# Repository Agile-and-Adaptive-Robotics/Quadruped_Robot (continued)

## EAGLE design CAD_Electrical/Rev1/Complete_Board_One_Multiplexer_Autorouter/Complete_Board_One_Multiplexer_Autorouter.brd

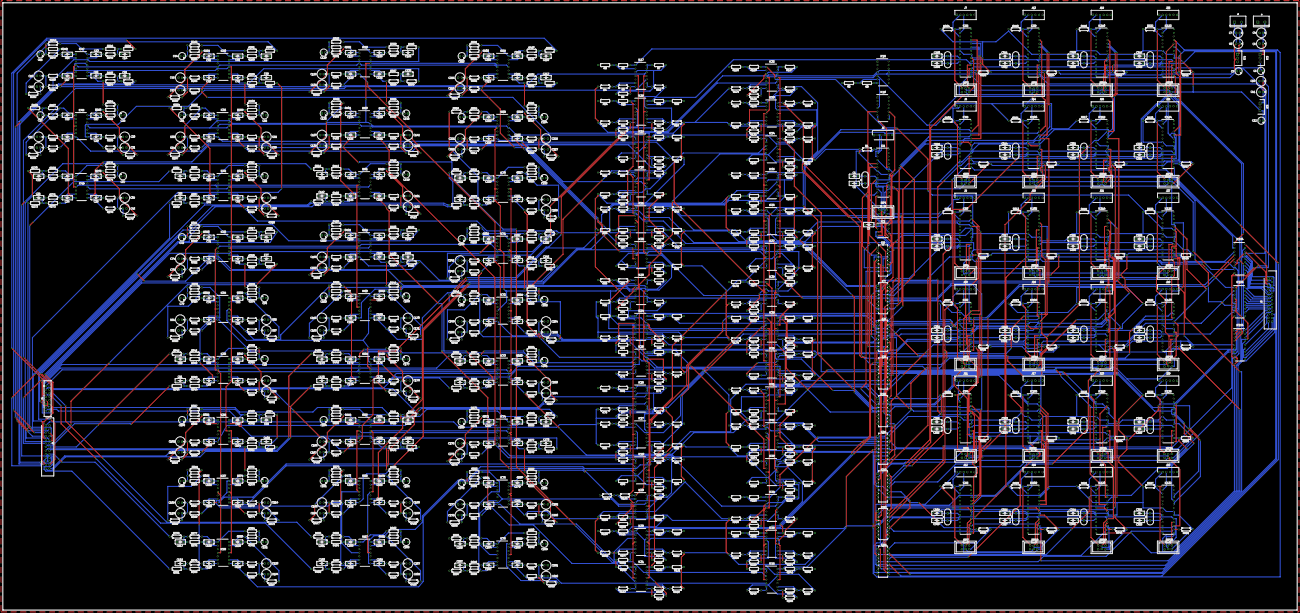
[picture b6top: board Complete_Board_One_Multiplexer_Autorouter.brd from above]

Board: 2 copper layers, 916.9 x 430.2 mm, 1174 parts (0 on the bottom side), 890 nets.

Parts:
C1, C2, C3, C13, C14, C15, C17, C20, C21, C22, C24, C27, C29, C32, C33, C34, C35, C36, C38, C41, C42, C43, C45, C48, C49, C50, C52, C55, C57, C60, C61, C62, C63, C64, C66, C69, C70, C71, C73, C76, C77, C78, C80, C83, C85, C88, C89, C90, C91, C92, C94, C97, C98, C99, C101, C104, C105, C106, C108, C111, C113, C116, C117, C118, C119, C120, C122, C125, C126, C127, C129, C132, C133, C134, C136, C139, C141, C144, C145, C146, C147, C148, C150, C153, C154, C155, C157, C160, C161, C162, C164, C167, C169, C172, C173, C174, C175, C176, C178, C181, C182, C183, C185, C188, C189, C190, C192, C195, C197, C200, C201, C202, C203, C204, C206, C209, C210, C211, C213, C216, C217, C218, C220, C223, C225, C228, C229, C230, C231, C232, C234, C237, C238, C239, C241, C244, C245, C246, C248, C251, C253, C256, C257, C258, C259, C260, C262, C265, C266, C267, C269, C272, C273, C274, C276, C279, C281, C284, C285, C286, C287, C288, C290, C293, C294, C296, C297, C299, C300, C302, C303, C305, C306, C308, C309, C311, C312, C314, C315, C317, C318, C320, C321, C323, C324, C326, C327, C329, C330, C332, C333, C335, C336, C338, C339, C341, C342, C344, C345, C347, C348, C350, C351, C353, C354, C356, C357, C359, C360, C362, C363: C050-030X075
C4, C5, C7, C8, C10, C11, C18, C19, C25, C26, C30, C31, C39, C40, C46, C47, C53, C54, C58, C59, C67, C68, C74, C75, C81, C82, C86, C87, C95, C96, C102, C103, C109, C110, C114, C115, C123, C124, C130, C131, C137, C138, C142, C143, C151, C152, C158, C159, C165, C166, C170, C171, C179, C180, C186, C187, C193, C194, C198, C199, C207, C208, C214, C215, C221, C222, C226, C227, C235, C236, C242, C243, C249, C250, C254, C255, C263, C264, C270, C271, C277, C278, C282, C283, C291, C292: E2,5-7
C6, C9, C12, C16, C23, C28, C37, C44, C51, C56, C65, C72, C79, C84, C93, C100, C107, C112, C121, C128, C135, C140, C149, C156, C163, C168, C177, C184, C191, C196, C205, C212, C219, C224, C233, C240, C247, C252, C261, C268, C275, C280, C289: E2,5-5
IC1, IC86, IC88, IC90, IC92, IC94, IC96, IC98, IC100, IC102, IC104, IC106, IC108, IC110, IC112, IC114, IC116, IC118, IC120, IC122, IC124, IC126, IC128, IC130, IC132: ATMEGA88A-PU; DIP794W53P254L3467H457Q28N
IC2: MCP4921-E_P; DIP781W56P254L950H533Q8N
IC3, IC4: L78S24CV; TO270P460X1020X2008-3P
IC5: L7805CV; TO270P460X1020X2008-3P
IC6, IC7, IC8, IC9, IC10, IC11, IC12, IC13, IC14: CD4051BE; DIP254P762X508-16
IC15, IC16, IC17, IC18, IC19, IC20, IC21, IC22, IC23, IC24, IC25, IC26, IC27, IC28, IC29, IC30, IC31, IC32, IC33, IC34, IC35, IC36, IC37, IC38, IC39, IC40, IC41, IC42, IC43, IC44, IC45, IC46, IC47, IC48, IC49, IC50, IC51, IC52, IC53, IC54, IC55, IC56, IC57, IC58, IC59, IC60, IC61, IC62, IC63, IC64, IC65, IC66, IC67, IC68, IC69, IC70, IC71, IC72, IC73, IC74, IC75, IC76: LM324N; DIP794W56P254L1905H533Q14N
IC134, IC135, IC136: TBD62783APG; DIP762W55P254L2286H480Q18N
ISP1, ISP2, ISP3, ISP4, ISP5, ISP6, ISP7, ISP8, ISP9, ISP10, ISP11, ISP12, ISP13, ISP14, ISP15, ISP16, ISP17, ISP18, ISP19, ISP20, ISP21, ISP22, ISP23, ISP24, ISP25: AVRISP-BOX
J1, J2: SCREWTERMINAL-5MM-2
J3, J5: 30326-6002HB; SHDR26W81P254_2X13_4060X840X94
J4: 30316-6002HB; 3M-30316-6002HB
J6, J7, J8, J9, J10, J11, J12, J13, J14, J15, J16, J17, J18, J19, J20, J21, J22, J23, J24, J25, J26, J27, J28, J29, J30: 22-23-2061; SHDR6W87P0X254_1X6_1509X635X10
R1, R2, R3, R4, R5, R6, R7, R8, R9, R10, R11, R12, R13, R14, R15, R16, R17, R18, R19, R20, R21, R22, R23, R24, R25, R26, R27, R28, R29, R30, R31, R32, R33, R34, R35, R36, R37, R38, R39, R40, R41, R42, R43, R44, R45, R46, R47, R48, R49, R50, R51, R52, R53, R54, R55, R56, R57, R58, R59, R60, R61, R62, R63, R64, R65, R66, R67, R68, R69, R70, R71, R72, R73, R74, R75, R76, R77, R78, R79, R80, R81, R82, R83, R84, R85, R86, R87, R88, R89, R90, R91, R92, R93, R94, R95, R96, R97, R98, R99, R100, R101, R102, R103, R104, R105, R106, R107, R108, R109, R110, R111, R112, R113, R114, R115, R116, R117, R118, R119, R120, R121, R122, R123, R124, R125, R126, R127, R128, R129, R130, R131, R132, R133, R134, R135, R136, R137, R138, R139, R140, R141, R142, R143, R144, R145, R146, R147, R148, R149, R150, R151, R152, R153, R154, R155, R156, R157, R158, R159, R160, R161, R162, R163, R164, R165, R166, R167, R168, R169, R170, R171, R172, R173, R174, R175, R176, R177, R178, R179, R180, R181, R182, R183, R184, R185, R186, R187, R188, R189, R190, R191, R192, R193, R194, R195, R196, R197, R198, R199, R200, R201, R202, R203, R204, R205, R206, R207, R208, R209, R210, R211, R212, R213, R214, R215, R216, R217, R218, R219, R220, R221, R222, R223, R224, R225, R226, R227, R228, R229, R230, R231, R232, R233, R234, R235, R236, R237, R238, R239, R240, R241, R242, R243, R244, R245, R246, R247, R248, R249, R250, R251, R252, R253, R254, R255, R256, R257, R258, R259, R260, R261, R262, R263, R264, R265, R266, R267, R268, R269, R270, R271, R272, R273, R274, R275, R276, R277, R278, R279, R280, R281, R282, R283, R284, R285, R286, R287, R288, R289, R290, R291, R292, R293, R294, R295, R296, R297, R298, R299, R300, R301, R302, R303, R304, R305, R306, R307, R308, R309, R310, R311, R312, R313, R314, R315, R316, R317, R318, R319, R320, R321, R322, R323, R324, R325, R326, R327, R328, R329, R330, R331, R332, R333, R334, R335, R336, R337, R338, R339, R340, R341, R342, R343, R344, R345, R346, R347, R348, R349, R350, R351, R352, R353, R354, R355, R356, R357, R358, R359, R360, R361, R362, R363, R364, R365, R366, R367, R368, R369, R370, R371, R372, R373, R374, R375, R376, R377, R378, R379, R380, R381, R382, R383, R384, R385, R386, R387, R388, R389, R390, R391, R392, R393, R394, R395, R396, R397, R398, R399, R400, R401, R402, R403, R404, R405, R406, R407, R408, R409, R410, R411, R412, R413, R414, R415, R416, R417, R418, R419, R420, R421, R422, R423, R424, R425, R426, R427, R428, R429, R430, R431, R432, R433, R434, R435, R436, R437, R438, R439, R440, R441, R442, R443, R444, R445, R446, R447, R448, R449, R450, R451, R452, R453, R454, R455, R456, R457, R458, R459, R460, R461, R462, R463, R464, R465, R466, R467, R468, R469, R470, R471, R472, R473, R474, R475, R476, R477, R478, R479, R480, R481, R482, R483, R484, R485, R486, R487, R488, R489, R490, R491, R492, R493, R494, R495, R496, R497, R498, R499, R500, R501, R502, R503, R504, R505, R506, R507, R508, R509, R510, R511, R512, R513, R514, R515, R516, R517, R518, R519, R520, R521, R522, R523, R524, R525, R526, R527, R528, R529, R530, R531, R532, R533, R534, R535, R536, R537, R538, R539, R540, R541, R542, R543, R544, R545, R546, R547, R548, R549, R550, R551, R552, R553, R554, R555, R556, R557, R558, R559, R560, R561, R562, R563, R564, R565, R566, R567, R568, R569, R570, R571, R572, R573, R574, R575, R576, R577, R578, R579, R580, R581, R582, R583, R584, R585, R586, R587, R588, R589, R590, R591, R592, R593, R594, R595, R596, R597, R598, R599, R600, R601, R602, R603, R604, R605, R606, R607, R608, R609, R610, R611, R612, R613, R614, R615, R616, R617, R618, R619, R620, R621, R622, R623, R624, R625, R626, R627, R628, R629, R630, R631, R632, R633, R634, R635, R636, R637, R638, R639, R640, R641, R642, R643, R644, R645, R646, R647, R648, R649, R650, R651: 0207/10
Y1, Y2, Y3, Y4, Y5, Y6, Y7, Y8, Y9, Y10, Y11, Y12, Y13, Y14, Y15, Y16, Y17, Y18, Y19, Y20, Y21, Y22, Y23, Y24, Y25: 16MHz; HC49US

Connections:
+5V: C3.1, C12.+, IC1.7, IC1.20, IC1.21, IC2.1, IC2.6, IC5.3, IC6.16, IC7.16, IC8.16, IC9.16, IC10.16, IC11.16, IC12.16, IC13.16, IC14.16, IC16.5, IC86.7, IC86.20, IC86.21, IC88.7, IC88.20, IC88.21, IC90.7, IC90.20, IC90.21, IC92.7, IC92.20, IC92.21, IC94.7, IC94.20, IC94.21, IC96.7, IC96.20, IC96.21, IC98.7, IC98.20, IC98.21, IC100.7, IC100.20, IC100.21, IC102.7, IC102.20, IC102.21, IC104.7, IC104.20, IC104.21, IC106.7, IC106.20, IC106.21, IC108.7, IC108.20, IC108.21, IC110.7, IC110.20, IC110.21, IC112.7, IC112.20, IC112.21, IC114.7, IC114.20, IC114.21, IC116.7, IC116.20, IC116.21, IC118.7, IC118.20, IC118.21, IC120.7, IC120.20, IC120.21, IC122.7, IC122.20, IC122.21, IC124.7, IC124.20, IC124.21, IC126.7, IC126.20, IC126.21, IC128.7, IC128.20, IC128.21, IC130.7, IC130.20, IC130.21, IC132.7, IC132.20, IC132.21, ISP1.2, ISP2.2, ISP3.2, ISP4.2, ISP5.2, ISP6.2, ISP7.2, ISP8.2, ISP9.2, ISP10.2, ISP11.2, ISP12.2, ISP13.2, ISP14.2, ISP15.2, ISP16.2, ISP17.2, ISP18.2, ISP19.2, ISP20.2, ISP21.2, ISP22.2, ISP23.2, ISP24.2, ISP25.2, J3.1, R1.1, R4.2, R10.2, R16.1, R22.1, R28.2, R34.2, R40.1, R46.1, R52.2, R58.2, R64.1, R70.1, R76.2, R82.2, R88.1, R94.1, R100.2, R106.2, R112.1, R118.1, R124.2, R130.2, R136.1, R142.1, R148.2, R154.2, R160.1, R166.1, R172.2, R178.2, R184.1, R190.1, R196.2, R202.2, R208.1, R214.1, R220.2, R226.2, R232.1, R238.1, R604.1, R605.1, R606.1, R607.1, R608.1, R609.1, R610.1, R611.1, R612.1, R613.1, R614.1, R615.1, R616.1, R617.1, R618.1, R619.1, R620.1, R621.1, R622.1, R623.1, R624.1, R625.1, R626.1, R627.1, R628.1, R629.1, R630.1, R631.1, R632.1, R633.1, R634.1, R635.1, R636.1, R637.1, R638.1, R639.1, R640.1, R641.1, R642.1, R643.1, R644.1, R645.1, R646.1, R647.1, R648.1, R649.1, R650.1, R651.1
+24V: C6.+, C10.+, C11.+, IC3.3, IC5.1, IC16.4, IC17.4, IC18.4, IC19.4, IC20.4, IC21.4, IC22.4, IC23.4, IC24.4, IC25.4, IC26.4, IC27.4, IC28.4, IC29.4, IC30.4, IC31.4, IC32.4, IC33.4, IC34.4, IC35.4, IC36.4, IC37.4, IC38.4, IC39.4, IC40.4, IC41.4, IC42.4, IC43.4, IC44.4, IC45.4, IC46.4, IC47.4, IC48.4, IC49.4, IC50.4, IC51.4, IC52.4, IC53.4, IC54.4, IC55.4, IC56.4, IC57.4, IC58.4, IC59.4, IC60.4, IC61.4, IC62.4, IC63.4, IC64.4, IC65.4, IC66.4, IC67.4, IC68.4, IC69.4, IC70.4, IC71.4, IC72.4, IC73.4, IC74.4, IC75.4, IC76.4, IC134.9, IC135.9, IC136.9, J4.1
-24V: C7.-, C8.-, C9.-, IC4.2, IC16.11, IC17.11, IC18.11, IC19.11, IC20.11, IC21.11, IC22.11, IC23.11, IC24.11, IC25.11, IC26.11, IC27.11, IC28.11, IC29.11, IC30.11, IC31.11, IC32.11, IC33.11, IC34.11, IC35.11, IC36.11, IC37.11, IC38.11, IC39.11, IC40.11, IC41.11, IC42.11, IC43.11, IC44.11, IC45.11, IC46.11, IC47.11, IC48.11, IC49.11, IC50.11, IC51.11, IC52.11, IC53.11, IC54.11, IC55.11, IC56.11, IC57.11, IC58.11, IC59.11, IC60.11, IC61.11, IC62.11, IC63.11, IC64.11, IC65.11, IC66.11, IC67.11, IC68.11, IC69.11, IC70.11, IC71.11, IC72.11, IC73.11, IC74.11, IC75.11, IC76.11, J2.1
A0: IC1.4, IC6.11
ADC00: IC1.23, IC15.6, IC15.7
B0: IC1.5, IC6.10
C0: IC1.6, IC6.9
D0: IC1.11, IC7.11, IC8.11, IC9.11, IC10.11, IC11.11, IC12.11, IC13.11, IC14.11
DAC00: IC2.8, IC15.10
DEMUXIN: IC15.8, IC15.9
E0: IC1.12, IC7.10, IC8.10, IC9.10, IC10.10, IC11.10, IC12.10, IC13.10, IC14.10
F0: IC1.13, IC7.9, IC8.9, IC9.9, IC10.9, IC11.9, IC12.9, IC13.9, IC14.9
FOUT00: C17.1, IC17.12, IC47.7, R251.1
FOUT01: C29.1, IC17.10, IC48.8, R266.2
FOUT02: C24.1, IC19.3, IC48.7, R260.1
FOUT03: C38.1, IC19.5, IC49.8, R278.2
FOUT04: C45.1, IC20.12, IC50.7, R287.1
FOUT05: C57.1, IC20.10, IC51.8, R302.2
FOUT06: C52.1, IC22.3, IC51.7, R296.1
FOUT07: C66.1, IC22.5, IC52.8, R314.2
FOUT08: C73.1, IC23.12, IC53.7, R323.1
FOUT09: C85.1, IC23.10, IC54.8, R338.2
FOUT10: C80.1, IC25.3, IC54.7, R332.1
FOUT11: C94.1, IC25.5, IC55.8, R350.2
FOUT12: C101.1, IC26.12, IC56.7, R359.1
FOUT13: C113.1, IC26.10, IC57.8, R374.2
FOUT14: C108.1, IC28.3, IC57.7, R368.1
FOUT15: C122.1, IC28.5, IC58.8, R386.2
FOUT16: C129.1, IC29.12, IC59.7, R395.1
FOUT17: C141.1, IC29.10, IC60.8, R410.2
FOUT18: C136.1, IC31.3, IC60.7, R404.1
FOUT19: C150.1, IC31.5, IC61.8, R422.2
FOUT20: C157.1, IC32.12, IC62.7, R431.1
FOUT21: C169.1, IC32.10, IC63.8, R446.2
FOUT22: C164.1, IC34.3, IC63.7, R440.1
FOUT23: C178.1, IC34.5, IC64.8, R458.2
FOUT24: C185.1, IC35.12, IC65.7, R467.1
FOUT25: C197.1, IC35.10, IC66.8, R482.2
FOUT26: C192.1, IC37.3, IC66.7, R476.1
FOUT27: C206.1, IC37.5, IC67.8, R494.2
FOUT28: C213.1, IC38.12, IC68.7, R503.1
FOUT29: C225.1, IC38.10, IC69.8, R518.2
FOUT30: C220.1, IC40.3, IC69.7, R512.1
FOUT31: C234.1, IC40.5, IC70.8, R530.2
FOUT32: C241.1, IC41.12, IC71.7, R539.1
FOUT33: C253.1, IC41.10, IC72.8, R554.2
FOUT34: C248.1, IC43.3, IC72.7, R548.1
FOUT35: C262.1, IC43.5, IC73.8, R566.2
FOUT36: C269.1, IC44.12, IC74.7, R575.1
FOUT37: C281.1, IC44.10, IC75.8, R590.2
FOUT38: C276.1, IC46.3, IC75.7, R584.1
FOUT39: C290.1, IC46.5, IC76.8, R602.2
GND: C1.2, C2.2, C3.2, C4.-, C5.-, C6.-, C9.+, C10.-, C11.-, C12.-, C14.2, C16.-, C18.-, C19.-, C21.2, C23.-, C25.-, C26.-, C28.-, C30.-, C31.-, C33.2, C35.2, C37.-, C39.-, C40.-, C42.2, C44.-, C46.-, C47.-, C49.2, C51.-, C53.-, C54.-, C56.-, C58.-, C59.-, C61.2, C63.2, C65.-, C67.-, C68.-, C70.2, C72.-, C74.-, C75.-, C77.2, C79.-, C81.-, C82.-, C84.-, C86.-, C87.-, C89.2, C91.2, C93.-, C95.-, C96.-, C98.2, C100.-, C102.-, C103.-, C105.2, C107.-, C109.-, C110.-, C112.-, C114.-, C115.-, C117.2, C119.2, C121.-, C123.-, C124.-, C126.2, C128.-, C130.-, C131.-, C133.2, C135.-, C137.-, C138.-, C140.-, C142.-, C143.-, C145.2, C147.2, C149.-, C151.-, C152.-, C154.2, C156.-, C158.-, C159.-, C161.2, C163.-, C165.-, C166.-, C168.-, C170.-, C171.-, C173.2, C175.2, C177.-, C179.-, C180.-, C182.2, C184.-, C186.-, C187.-, C189.2, C191.-, C193.-, C194.-, C196.-, C198.-, C199.-, C201.2, C203.2, C205.-, C207.-, C208.-, C210.2, C212.-, C214.-, C215.-, C217.2, C219.-, C221.-, C222.-, C224.-, C226.-, C227.-, C229.2, C231.2, C233.-, C235.-, C236.-, C238.2, C240.-, C242.-, C243.-, C245.2, C247.-, C249.-, C250.-, C252.-, C254.-, C255.-, C257.2, C259.2, C261.-, C263.-, C264.-, C266.2, C268.-, C270.-, C271.-, C273.2, C275.-, C277.-, C278.-, C280.-, C282.-, C283.-, C285.2, C287.2, C289.-, C291.-, C292.-, C293.2, C294.2, C296.2, C297.2, C299.2, C300.2, C302.2, C303.2, C305.2, C306.2, C308.2, C309.2, C311.2, C312.2, C314.2, C315.2, C317.2, C318.2, C320.2, C321.2, C323.2, C324.2, C326.2, C327.2, C329.2, C330.2, C332.2, C333.2, C335.2, C336.2, C338.2, C339.2, C341.2, C342.2, C344.2, C345.2, C347.2, C348.2, C350.2, C351.2, C353.2, C354.2, C356.2, C357.2, C359.2, C360.2, C362.2, C363.2, IC1.8, IC1.22, IC2.7, IC3.2, IC4.3, IC5.2, IC6.6, IC6.7, IC6.8, IC7.6, IC7.7, IC7.8, IC8.6, IC8.7, IC8.8, IC9.6, IC9.7, IC9.8, IC10.6, IC10.7, IC10.8, IC11.6, IC11.7, IC11.8, IC12.6, IC12.7, IC12.8, IC13.6, IC13.7, IC13.8, IC14.6, IC14.7, IC14.8, IC15.11, IC17.5, IC18.5, IC18.10, IC19.10, IC20.5, IC21.5, IC21.10, IC22.10, IC23.5, IC24.5, IC24.10, IC25.10, IC26.5, IC27.5, IC27.10, IC28.10, IC29.5, IC30.5, IC30.10, IC31.10, IC32.5, IC33.5, IC33.10, IC34.10, IC35.5, IC36.5, IC36.10, IC37.10, IC38.5, IC39.5, IC39.10, IC40.10, IC41.5, IC42.5, IC42.10, IC43.10, IC44.5, IC45.5, IC45.10, IC46.10, IC47.3, IC47.5, IC47.10, IC47.12, IC48.3, IC48.5, IC48.10, IC48.12, IC49.3, IC49.5, IC49.10, IC49.12, IC50.3, IC50.5, IC50.10, IC50.12, IC51.3, IC51.5, IC51.10, IC51.12, IC52.3, IC52.5, IC52.10, IC52.12, IC53.3, IC53.5, IC53.10, IC53.12, IC54.3, IC54.5, IC54.10, IC54.12, IC55.3, IC55.5, IC55.10, IC55.12, IC56.3, IC56.5, IC56.10, IC56.12, IC57.3, IC57.5, IC57.10, IC57.12, IC58.3, IC58.5, IC58.10, IC58.12, IC59.3, IC59.5, IC59.10, IC59.12, IC60.3, IC60.5, IC60.10, IC60.12, IC61.3, IC61.5, IC61.10, IC61.12, IC62.3, IC62.5, IC62.10, IC62.12, IC63.3, IC63.5, IC63.10, IC63.12, IC64.3, IC64.5, IC64.10, IC64.12, IC65.3, IC65.5, IC65.10, IC65.12, IC66.3, IC66.5, IC66.10, IC66.12, IC67.3, IC67.5, IC67.10, IC67.12, IC68.3, IC68.5, IC68.10, IC68.12, IC69.3, IC69.5, IC69.10, IC69.12, IC70.3, IC70.5, IC70.10, IC70.12, IC71.3, IC71.5, IC71.10, IC71.12, IC72.3, IC72.5, IC72.10, IC72.12, IC73.3, IC73.5, IC73.10, IC73.12, IC74.3, IC74.5, IC74.10, IC74.12, IC75.3, IC75.5, IC75.10, IC75.12, IC76.3, IC76.5, IC76.10, IC76.12, IC86.8, IC86.22, IC88.8, IC88.22, IC90.8, IC90.22, IC92.8, IC92.22, IC94.8, IC94.22, IC96.8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
MISO00: IC1.18, ISP1.1
MISO01: IC86.18, ISP2.1
MISO02: IC88.18, ISP3.1
MISO03: IC90.18, ISP4.1
MISO04: IC92.18, ISP5.1
MISO05: IC94.18, ISP6.1
MISO06: IC96.18, ISP7.1
MISO07: IC98.18, ISP8.1
MISO08: IC100.18, ISP9.1
MISO09: IC102.18, ISP10.1
MISO10: IC104.18, ISP11.1
MISO11: IC106.18, ISP12.1
MISO12: IC108.18, ISP13.1
MISO13: IC110.18, ISP14.1
MISO14: IC112.18, ISP15.1
MISO15: IC114.18, ISP16.1
MISO16: IC116.18, ISP17.1
MISO17: IC118.18, ISP18.1
MISO18: IC120.18, ISP19.1
MISO19: IC122.18, ISP20.1
MISO20: IC124.18, ISP21.1
MISO21: IC126.18, ISP22.1
MISO22: IC128.18, ISP23.1
MISO23: IC130.18, ISP24.1
MISO24: IC132.18, ISP25.1
MOSI00: IC1.17, IC2.4, IC86.17, IC88.17, IC90.17, IC92.17, IC94.17, IC96.17, IC98.17, IC100.17, IC102.17, IC104.17, IC106.17, IC108.17, IC110.17, IC112.17, IC114.17, IC116.17, IC118.17, IC120.17, IC122.17, IC124.17, IC126.17, IC128.17, IC130.17, IC132.17, ISP1.4, ISP2.4, ISP3.4, ISP4.4, ISP5.4, ISP6.4, ISP7.4, ISP8.4, ISP9.4, ISP10.4, ISP11.4, ISP12.4, ISP13.4, ISP14.4, ISP15.4, ISP16.4, ISP17.4, ISP18.4, ISP19.4, ISP20.4, ISP21.4, ISP22.4, ISP23.4, ISP24.4, ISP25.4
MUX00: IC7.13, IC17.1, IC86.23, IC88.24, R9.1
MUX01: IC7.14, IC18.14, IC86.24, IC88.23, R21.1
MUX02: IC7.15, IC18.1, IC90.23, IC92.24, R15.1
MUX03: IC7.12, IC19.14, IC90.24, IC92.23, R27.1
MUX04: IC7.1, IC20.1, IC94.23, IC96.24, R33.1
MUX05: IC7.5, IC21.14, IC94.24, IC96.23, R45.1
MUX06: IC7.2, IC21.1, IC98.23, IC100.24, R39.1
MUX07: IC7.4, IC22.14, IC98.24, IC100.23, R50.1
MUX08: IC8.13, IC23.1, IC102.23, IC104.24, R57.1
MUX09: IC8.14, IC24.14, IC102.24, IC104.23, R69.1
MUX10: IC8.15, IC24.1, IC106.23, IC108.24, R63.1
MUX11: IC8.12, IC25.14, IC106.24, IC108.23, R74.1
MUX12: IC8.1, IC26.1, IC110.23, IC112.24, R81.1
MUX13: IC8.5, IC27.14, IC110.24, IC112.23, R93.1
MUX14: IC8.2, IC27.1, IC114.23, IC116.24, R87.1
MUX15: IC8.4, IC28.14, IC114.24, IC116.23, R98.1
MUX16: IC9.13, IC29.1, IC118.23, IC120.24, R105.1
MUX17: IC9.14, IC30.14, IC118.24, IC120.23, R117.1
MUX18: IC9.15, IC30.1, IC122.23, IC124.24, R111.1
MUX19: IC9.12, IC31.14, IC122.24, IC124.23, R122.1
MUX20: IC9.1, IC32.1, IC126.23, IC128.24, R129.1
MUX21: IC9.5, IC33.14, IC126.24, IC128.23, R141.1
MUX22: IC9.2, IC33.1, IC130.23, IC132.24, R135.1
MUX23: IC9.4, IC34.14, IC130.24, IC132.23, R146.1
MUX24: IC10.13, IC35.1, IC86.25, IC88.25, R153.1
MUX25: IC10.14, IC36.14, IC90.25, IC92.25, R165.1
MUX26: IC10.15, IC36.1, IC90.26, IC92.26, R159.1
MUX27: IC10.12, IC37.14, IC94.25, IC96.25, R170.1
MUX28: IC10.1, IC38.1, IC98.25, IC100.25, R177.1
MUX29: IC10.5, IC39.14, IC102.25, IC104.25, R189.1
MUX30: IC10.2, IC39.1, IC106.25, IC108.25, R183.1
MUX31: IC10.4, IC40.14, IC110.25, IC112.25, R194.1
MUX32: IC11.13, IC41.1, IC114.25, IC116.25, R201.1
MUX33: IC11.14, IC42.14, IC114.26, IC116.26, R213.1
MUX34: IC11.15, IC42.1, IC118.25, IC120.25, R207.1
MUX35: IC11.12, IC43.14, IC122.25, IC124.25, R218.1
MUX36: IC11.1, IC44.1, IC126.25, IC128.25, R225.1
MUX37: IC11.5, IC45.14, IC130.25, IC132.25, R237.1
MUX38: IC11.2, IC45.1, R231.1
MUX39: IC11.4, IC46.14, R242.1
MUX40: IC12.13, IC86.16, R628.2
MUX41: IC12.14, IC88.16, R629.2
MUX42: IC12.15, IC90.16, R630.2
MUX43: IC12.12, IC92.16, R631.2
MUX44: IC12.1, IC94.16, R632.2
MUX45: IC12.5, IC96.16, R633.2
MUX46: IC12.2, IC98.16, R634.2
MUX47: IC12.4, IC100.16, R635.2
MUX48: IC13.13, IC102.16, R636.2
MUX49: IC13.14, IC104.16, R637.2
MUX50: IC13.15, IC106.16, R638.2
MUX51: IC13.12, IC108.16, R639.2
MUX52: IC13.1, IC110.16, R640.2
MUX53: IC13.5, IC112.16, R641.2
MUX54: IC13.2, IC114.16, R642.2
MUX55: IC13.4, IC116.16, R643.2
MUX56: IC14.13, IC118.16, R644.2
MUX57: IC14.14, IC120.16, R645.2
MUX58: IC14.15, IC122.16, R646.2
MUX59: IC14.12, IC124.16, R647.2
MUX60: IC14.1, IC126.16, R648.2
MUX61: IC14.5, IC128.16, R649.2
MUX62: IC14.2, IC130.16, R650.2
MUX63: IC14.4, IC132.16, R651.2
MUXOUT: IC6.3, IC15.5
unnamed: C2.1, IC1.10, Y1.1
unnamed: IC15.4, IC16.6, R2.1, R3.1
unnamed: IC6.13, IC7.3
unnamed: IC1.14, IC2.2
unnamed: IC1.15, IC2.5
unnamed: IC6.14, IC8.3
unnamed: IC6.15, IC9.3
unnamed: IC6.12, IC10.3
unnamed: IC6.1, IC11.3
unnamed: IC6.5, IC12.3
unnamed: C1.1, IC1.9, Y1.2
unnamed: IC6.2, IC13.3
unnamed: IC6.4, IC14.3
unnamed: IC16.7, R3.2
unnamed: IC17.13, IC17.14, R7.2
unnamed: IC17.6, R4.1, R5.1
unnamed: IC17.7, R5.2, R6.1
unnamed: IC17.3, R6.2, R7.1
unnamed: IC17.2, R8.1, R9.2
unnamed: IC20.13, IC20.14, R31.2
unnamed: IC20.6, R28.1, R29.1
unnamed: IC18.6, R10.1, R11.1
unnamed: IC18.7, R11.2, R12.1
unnamed: IC18.3, R12.2, R13.1
unnamed: IC18.2, R14.1, R15.2
unnamed: IC20.7, R29.2, R30.1
unnamed: IC20.3, R30.2, R31.1
unnamed: IC17.8, IC17.9, R19.2
unnamed: IC18.13, R20.1, R21.2
unnamed: IC19.1, IC19.2, R13.2
unnamed: IC18.12, R18.2, R19.1
unnamed: IC18.9, R16.2, R17.2
unnamed: IC18.8, R17.1, R18.1
unnamed: IC19.13, R26.1, R27.2
unnamed: IC19.12, R24.2, R25.2
unnamed: IC19.9, R22.2, R23.2
unnamed: IC19.8, R23.1, R24.1
unnamed: IC19.6, IC19.7, R25.1
unnamed: IC20.2, R32.1, R33.2
unnamed: IC21.6, R34.1, R35.1
unnamed: IC21.7, R35.2, R36.1
unnamed: IC21.3, R36.2, R37.1
unnamed: IC21.2, R38.1, R39.2
unnamed: IC20.8, IC20.9, R43.2
unnamed: IC21.13, R44.1, R45.2
unnamed: IC21.12, R42.2, R43.1
unnamed: IC21.9, R40.2, R41.2
unnamed: IC21.8, R41.1, R42.1
unnamed: IC22.1, IC22.2, R37.2
unnamed: IC22.13, R49.1, R50.2
unnamed: IC22.12, R48.2, R51.2
unnamed: IC22.9, R46.2, R47.2
unnamed: IC22.8, R47.1, R48.1
unnamed: IC22.6, IC22.7, R51.1
unnamed: IC23.13, IC23.14, R55.2
unnamed: IC23.6, R52.1, R53.1
unnamed: IC23.7, R53.2, R54.1
unnamed: IC23.3, R54.2, R55.1
unnamed: IC23.2, R56.1, R57.2
unnamed: IC24.6, R58.1, R59.1
unnamed: IC24.7, R59.2, R60.1
unnamed: IC24.3, R60.2, R61.1
unnamed: IC24.2, R62.1, R63.2
unnamed: IC23.8, IC23.9, R67.2
unnamed: IC24.13, R68.1, R69.2
unnamed: IC24.12, R66.2, R67.1
unnamed: IC24.9, R64.2, R65.2
unnamed: IC24.8, R65.1, R66.1
unnamed: IC25.1, IC25.2, R61.2
unnamed: IC25.13, R73.1, R74.2
unnamed: IC25.12, R72.2, R75.2
unnamed: IC25.9, R70.2, R71.2
unnamed: IC25.8, R71.1, R72.1
unnamed: IC25.6, IC25.7, R75.1
unnamed: IC26.13, IC26.14, R79.2
unnamed: IC26.6, R76.1, R77.1
unnamed: IC26.7, R77.2, R78.1
unnamed: IC26.3, R78.2, R79.1
unnamed: IC26.2, R80.1, R81.2
unnamed: IC27.6, R82.1, R83.1
unnamed: IC27.7, R83.2, R84.1
unnamed: IC27.3, R84.2, R85.1
unnamed: IC27.2, R86.1, R87.2
unnamed: IC26.8, IC26.9, R91.2
unnamed: IC27.13, R92.1, R93.2
unnamed: IC27.12, R90.2, R91.1
unnamed: IC27.9, R88.2, R89.2
unnamed: IC27.8, R89.1, R90.1
unnamed: IC28.1, IC28.2, R85.2
unnamed: IC28.13, R97.1, R98.2
unnamed: IC28.12, R96.2, R99.2
unnamed: IC28.9, R94.2, R95.2
unnamed: IC28.8, R95.1, R96.1
unnamed: IC28.6, IC28.7, R99.1
unnamed: IC29.13, IC29.14, R103.2
unnamed: IC29.6, R100.1, R101.1
unnamed: IC29.7, R101.2, R102.1
unnamed: IC29.3, R102.2, R103.1
unnamed: IC29.2, R104.1, R105.2
unnamed: IC30.6, R106.1, R107.1
unnamed: IC30.7, R107.2, R108.1
unnamed: IC30.3, R108.2, R109.1
unnamed: IC30.2, R110.1, R111.2
unnamed: IC29.8, IC29.9, R115.2
unnamed: IC30.13, R116.1, R117.2
unnamed: IC30.12, R114.2, R115.1
unnamed: IC30.9, R112.2, R113.2
unnamed: IC30.8, R113.1, R114.1
unnamed: IC31.1, IC31.2, R109.2
unnamed: IC31.13, R121.1, R122.2
unnamed: IC31.12, R120.2, R123.2
unnamed: IC31.9, R118.2, R119.2
unnamed: IC31.8, R119.1, R120.1
unnamed: IC31.6, IC31.7, R123.1
unnamed: IC32.13, IC32.14, R127.2
unnamed: IC32.6, R124.1, R125.1
unnamed: IC32.7, R125.2, R126.1
unnamed: IC32.3, R126.2, R127.1
unnamed: IC32.2, R128.1, R129.2
unnamed: IC33.6, R130.1, R131.1
unnamed: IC33.7, R131.2, R132.1
unnamed: IC33.3, R132.2, R133.1
unnamed: IC33.2, R134.1, R135.2
unnamed: IC32.8, IC32.9, R139.2
unnamed: IC33.13, R140.1, R141.2
unnamed: IC33.12, R138.2, R139.1
unnamed: IC33.9, R136.2, R137.2
unnamed: IC33.8, R137.1, R138.1
unnamed: IC34.1, IC34.2, R133.2
unnamed: IC34.13, R145.1, R146.2
unnamed: IC34.12, R144.2, R147.2
unnamed: IC34.9, R142.2, R143.2
unnamed: IC34.8, R143.1, R144.1
unnamed: IC34.6, IC34.7, R147.1
unnamed: IC35.13, IC35.14, R151.2
unnamed: IC35.6, R148.1, R149.1
unnamed: IC35.7, R149.2, R150.1
unnamed: IC35.3, R150.2, R151.1
unnamed: IC35.2, R152.1, R153.2
unnamed: IC36.6, R154.1, R155.1
unnamed: IC36.7, R155.2, R156.1
unnamed: IC36.3, R156.2, R157.1
unnamed: IC36.2, R158.1, R159.2
unnamed: IC35.8, IC35.9, R163.2
unnamed: IC36.13, R164.1, R165.2
unnamed: IC36.12, R162.2, R163.1
unnamed: IC36.9, R160.2, R161.2
unnamed: IC36.8, R161.1, R162.1
unnamed: IC37.1, IC37.2, R157.2
unnamed: IC37.13, R169.1, R170.2
unnamed: IC37.12, R168.2, R171.2
unnamed: IC37.9, R166.2, R167.2
unnamed: IC37.8, R167.1, R168.1
unnamed: IC37.6, IC37.7, R171.1
unnamed: IC38.13, IC38.14, R175.2
unnamed: IC38.6, R172.1, R173.1
unnamed: IC38.7, R173.2, R174.1
unnamed: IC38.3, R174.2, R175.1
unnamed: IC38.2, R176.1, R177.2
unnamed: IC39.6, R178.1, R179.1
unnamed: IC39.7, R179.2, R180.1
unnamed: IC39.3, R180.2, R181.1
unnamed: IC39.2, R182.1, R183.2
unnamed: IC38.8, IC38.9, R187.2
unnamed: IC39.13, R188.1, R189.2
unnamed: IC39.12, R186.2, R187.1
unnamed: IC39.9, R184.2, R185.2
unnamed: IC39.8, R185.1, R186.1
unnamed: IC40.1, IC40.2, R181.2
unnamed: IC40.13, R193.1, R194.2
unnamed: IC40.12, R192.2, R195.2
unnamed: IC40.9, R190.2, R191.2
unnamed: IC40.8, R191.1, R192.1
unnamed: IC40.6, IC40.7, R195.1
unnamed: IC41.13, IC41.14, R199.2
unnamed: IC41.6, R196.1, R197.1
unnamed: IC41.7, R197.2, R198.1
unnamed: IC41.3, R198.2, R199.1
unnamed: IC41.2, R200.1, R201.2
unnamed: IC42.6, R202.1, R203.1
unnamed: IC42.7, R203.2, R204.1
unnamed: IC42.3, R204.2, R205.1
unnamed: IC42.2, R206.1, R207.2
unnamed: IC41.8, IC41.9, R211.2
unnamed: IC42.13, R212.1, R213.2
unnamed: IC42.12, R210.2, R211.1
unnamed: IC42.9, R208.2, R209.2
unnamed: IC42.8, R209.1, R210.1
unnamed: IC43.1, IC43.2, R205.2
unnamed: IC43.13, R217.1, R218.2
unnamed: IC43.12, R216.2, R219.2
unnamed: IC43.9, R214.2, R215.2
unnamed: IC43.8, R215.1, R216.1
unnamed: IC43.6, IC43.7, R219.1
unnamed: IC44.13, IC44.14, R223.2
unnamed: IC44.6, R220.1, R221.1
unnamed: IC44.7, R221.2, R222.1
unnamed: IC44.3, R222.2, R223.1
unnamed: IC44.2, R224.1, R225.2
unnamed: IC45.6, R226.1, R227.1
unnamed: IC45.7, R227.2, R228.1
unnamed: IC45.3, R228.2, R229.1
unnamed: IC45.2, R230.1, R231.2
unnamed: IC44.8, IC44.9, R235.2
unnamed: IC45.13, R236.1, R237.2
unnamed: IC45.12, R234.2, R235.1
unnamed: IC45.9, R232.2, R233.2
unnamed: IC45.8, R233.1, R234.1
unnamed: IC46.1, IC46.2, R229.2
unnamed: IC46.13, R241.1, R242.2
unnamed: IC46.12, R240.2, R243.2
unnamed: IC46.9, R238.2, R239.2
unnamed: IC46.8, R239.1, R240.1
unnamed: IC46.6, IC46.7, R243.1
unnamed: C13.1, IC47.14, R245.2, R249.1
unnamed: C13.2, IC47.13, R244.2
unnamed: C14.1, R244.1, R245.1, R246.2
unnamed: C15.1, IC47.1, R248.1, R252.1
unnamed: C41.1, IC50.14, R281.2, R285.1
unnamed: C15.2, IC47.2, R247.1
unnamed: C41.2, IC50.13, R280.2
unnamed: C17.2, IC47.6, R250.1
unnamed: C16.+, R247.2, R248.2, R249.2
unnamed: C18.+, C19.+, R250.2, R251.2, R252.2
unnamed: C20.1, IC47.8, R254.2, R264.2
unnamed: C20.2, IC47.9, R253.2
unnamed: C21.1, R253.1, R254.1, R255.2
unnamed: C27.1, IC48.14, R263.2, R267.2
unnamed: C27.2, IC48.13, R262.2
unnamed: C28.+, R262.1, R263.1, R264.1
unnamed: C42.1, R280.1, R281.1, R282.2
unnamed: C43.1, IC50.1, R284.1, R288.1
unnamed: C22.1, IC48.1, R257.1, R261.1
unnamed: C22.2, IC48.2, R256.1
unnamed: C23.+, R256.2, R257.2, R258.1
unnamed: C43.2, IC50.2, R283.1
unnamed: C24.2, IC48.6, R259.1
unnamed: C25.+, C26.+, R259.2, R260.2, R261.2
unnamed: C29.2, IC48.9, R265.2
unnamed: C30.+, C31.+, R265.1, R266.1, R267.1
unnamed: C44.+, R283.2, R284.2, R285.2
unnamed: C32.2, IC49.2, R268.1
unnamed: C34.1, IC49.7, R258.2, R272.1
unnamed: C34.2, IC49.6, R271.1
unnamed: C33.1, R268.2, R269.2, R270.1
unnamed: C45.2, IC50.6, R286.1
unnamed: C46.+, C47.+, R286.2, R287.2, R288.2
unnamed: C35.1, R271.2, R272.2, R273.1
unnamed: C32.1, IC49.1, R269.1, R276.2
unnamed: C36.1, IC49.14, R275.2, R279.2
unnamed: C36.2, IC49.13, R274.2
unnamed: C37.+, R274.1, R275.1, R276.1
unnamed: C48.1, IC50.8, R290.2, R300.2
unnamed: C38.2, IC49.9, R277.2
unnamed: C39.+, C40.+, R277.1, R278.1, R279.1
unnamed: C48.2, IC50.9, R289.2
unnamed: C49.1, R289.1, R290.1, R291.2
unnamed: C50.1, IC51.1, R293.1, R297.1
unnamed: C50.2, IC51.2, R292.1
unnamed: C51.+, R292.2, R293.2, R294.1
unnamed: C52.2, IC51.6, R295.1
unnamed: C53.+, C54.+, R295.2, R296.2, R297.2
unnamed: C55.1, IC51.14, R299.2, R303.2
unnamed: C55.2, IC51.13, R298.2
unnamed: C56.+, R298.1, R299.1, R300.1
unnamed: C57.2, IC51.9, R301.2
unnamed: C58.+, C59.+, R301.1, R302.1, R303.1
unnamed: C60.2, IC52.2, R304.1
unnamed: C61.1, R304.2, R305.2, R306.1
unnamed: C62.1, IC52.7, R294.2, R308.1
unnamed: C62.2, IC52.6, R307.1
unnamed: C63.1, R307.2, R308.2, R309.1
unnamed: C60.1, IC52.1, R305.1, R312.2
unnamed: C64.1, IC52.14, R311.2, R315.2
unnamed: C64.2, IC52.13, R310.2
unnamed: C65.+, R310.1, R311.1, R312.1
unnamed: C66.2, IC52.9, R313.2
unnamed: C67.+, C68.+, R313.1, R314.1, R315.1
unnamed: C69.1, IC53.14, R317.2, R321.1
unnamed: C69.2, IC53.13, R316.2
unnamed: C70.1, R316.1, R317.1, R318.2
unnamed: C71.1, IC53.1, R320.1, R324.1
unnamed: C71.2, IC53.2, R319.1
unnamed: C72.+, R319.2, R320.2, R321.2
unnamed: C73.2, IC53.6, R322.1
unnamed: C74.+, C75.+, R322.2, R323.2, R324.2
unnamed: C76.1, IC53.8, R326.2, R336.2
unnamed: C76.2, IC53.9, R325.2
unnamed: C77.1, R325.1, R326.1, R327.2
unnamed: C78.1, IC54.1, R329.1, R333.1
unnamed: C78.2, IC54.2, R328.1
unnamed: C79.+, R328.2, R329.2, R330.1
unnamed: C80.2, IC54.6, R331.1
unnamed: C81.+, C82.+, R331.2, R332.2, R333.2
unnamed: C83.1, IC54.14, R335.2, R339.2
unnamed: C83.2, IC54.13, R334.2
unnamed: C84.+, R334.1, R335.1, R336.1
unnamed: C85.2, IC54.9, R337.2
unnamed: C86.+, C87.+, R337.1, R338.1, R339.1
unnamed: C88.2, IC55.2, R340.1
unnamed: C89.1, R340.2, R341.2, R342.1
unnamed: C90.1, IC55.7, R330.2, R344.1
unnamed: C90.2, IC55.6, R343.1
unnamed: C91.1, R343.2, R344.2, R345.1
unnamed: C88.1, IC55.1, R341.1, R348.2
unnamed: C92.1, IC55.14, R347.2, R351.2
unnamed: C92.2, IC55.13, R346.2
unnamed: C93.+, R346.1, R347.1, R348.1
unnamed: C94.2, IC55.9, R349.2
unnamed: C95.+, C96.+, R349.1, R350.1, R351.1
unnamed: C97.1, IC56.14, R353.2, R357.1
unnamed: C97.2, IC56.13, R352.2
unnamed: C98.1, R352.1, R353.1, R354.2
unnamed: C99.1, IC56.1, R356.1, R360.1
unnamed: C99.2, IC56.2, R355.1
unnamed: C100.+, R355.2, R356.2, R357.2
unnamed: C101.2, IC56.6, R358.1
unnamed: C102.+, C103.+, R358.2, R359.2, R360.2
unnamed: C104.1, IC56.8, R362.2, R372.2
unnamed: C104.2, IC56.9, R361.2
unnamed: C105.1, R361.1, R362.1, R363.2
unnamed: C106.1, IC57.1, R365.1, R369.1
unnamed: C106.2, IC57.2, R364.1
unnamed: C107.+, R364.2, R365.2, R366.1
unnamed: C108.2, IC57.6, R367.1
unnamed: C109.+, C110.+, R367.2, R368.2, R369.2
unnamed: C111.1, IC57.14, R371.2, R375.2
unnamed: C111.2, IC57.13, R370.2
unnamed: C112.+, R370.1, R371.1, R372.1
unnamed: C113.2, IC57.9, R373.2
unnamed: C114.+, C115.+, R373.1, R374.1, R375.1
unnamed: C116.2, IC58.2, R376.1
unnamed: C117.1, R376.2, R377.2, R378.1
unnamed: C118.1, IC58.7, R366.2, R380.1
unnamed: C118.2, IC58.6, R379.1
unnamed: C119.1, R379.2, R380.2, R381.1
unnamed: C116.1, IC58.1, R377.1, R384.2
unnamed: C120.1, IC58.14, R383.2, R387.2
unnamed: C120.2, IC58.13, R382.2
unnamed: C121.+, R382.1, R383.1, R384.1
unnamed: C122.2, IC58.9, R385.2
unnamed: C123.+, C124.+, R385.1, R386.1, R387.1
unnamed: C125.1, IC59.14, R389.2, R393.1
unnamed: C125.2, IC59.13, R388.2
unnamed: C126.1, R388.1, R389.1, R390.2
unnamed: C127.1, IC59.1, R392.1, R396.1
unnamed: C127.2, IC59.2, R391.1
unnamed: C128.+, R391.2, R392.2, R393.2
unnamed: C129.2, IC59.6, R394.1
unnamed: C130.+, C131.+, R394.2, R395.2, R396.2
unnamed: C132.1, IC59.8, R398.2, R408.2
unnamed: C132.2, IC59.9, R397.2
unnamed: C133.1, R397.1, R398.1, R399.2
unnamed: C134.1, IC60.1, R401.1, R405.1
unnamed: C134.2, IC60.2, R400.1
unnamed: C135.+, R400.2, R401.2, R402.1
unnamed: C136.2, IC60.6, R403.1
unnamed: C137.+, C138.+, R403.2, R404.2, R405.2
unnamed: C139.1, IC60.14, R407.2, R411.2
unnamed: C139.2, IC60.13, R406.2
unnamed: C140.+, R406.1, R407.1, R408.1
unnamed: C141.2, IC60.9, R409.2
unnamed: C142.+, C143.+, R409.1, R410.1, R411.1
unnamed: C144.2, IC61.2, R412.1
unnamed: C145.1, R412.2, R413.2, R414.1
unnamed: C146.1, IC61.7, R402.2, R416.1
unnamed: C146.2, IC61.6, R415.1
unnamed: C147.1, R415.2, R416.2, R417.1
unnamed: C144.1, IC61.1, R413.1, R420.2
unnamed: C148.1, IC61.14, R419.2, R423.2
unnamed: C148.2, IC61.13, R418.2
unnamed: C149.+, R418.1, R419.1, R420.1
unnamed: C150.2, IC61.9, R421.2
unnamed: C151.+, C152.+, R421.1, R422.1, R423.1
unnamed: C153.1, IC62.14, R425.2, R429.1
unnamed: C153.2, IC62.13, R424.2
unnamed: C154.1, R424.1, R425.1, R426.2
unnamed: C155.1, IC62.1, R428.1, R432.1
unnamed: C155.2, IC62.2, R427.1
unnamed: C156.+, R427.2, R428.2, R429.2
unnamed: C157.2, IC62.6, R430.1
unnamed: C158.+, C159.+, R430.2, R431.2, R432.2
unnamed: C160.1, IC62.8, R434.2, R444.2
unnamed: C160.2, IC62.9, R433.2
unnamed: C161.1, R433.1, R434.1, R435.2
unnamed: C162.1, IC63.1, R437.1, R441.1
unnamed: C162.2, IC63.2, R436.1
unnamed: C163.+, R436.2, R437.2, R438.1
unnamed: C164.2, IC63.6, R439.1
unnamed: C165.+, C166.+, R439.2, R440.2, R441.2
unnamed: C167.1, IC63.14, R443.2, R447.2
unnamed: C167.2, IC63.13, R442.2
unnamed: C168.+, R442.1, R443.1, R444.1
unnamed: C169.2, IC63.9, R445.2
unnamed: C170.+, C171.+, R445.1, R446.1, R447.1
unnamed: C172.2, IC64.2, R448.1
unnamed: C173.1, R448.2, R449.2, R450.1
unnamed: C174.1, IC64.7, R438.2, R452.1
unnamed: C174.2, IC64.6, R451.1
unnamed: C175.1, R451.2, R452.2, R453.1
unnamed: C172.1, IC64.1, R449.1, R456.2
unnamed: C176.1, IC64.14, R455.2, R459.2
unnamed: C176.2, IC64.13, R454.2
unnamed: C177.+, R454.1, R455.1, R456.1
unnamed: C178.2, IC64.9, R457.2
unnamed: C179.+, C180.+, R457.1, R458.1, R459.1
unnamed: C181.1, IC65.14, R461.2, R465.1
unnamed: C181.2, IC65.13, R460.2
unnamed: C182.1, R460.1, R461.1, R462.2
unnamed: C183.1, IC65.1, R464.1, R468.1
unnamed: C183.2, IC65.2, R463.1
unnamed: C184.+, R463.2, R464.2, R465.2
unnamed: C185.2, IC65.6, R466.1
unnamed: C186.+, C187.+, R466.2, R467.2, R468.2
unnamed: C188.1, IC65.8, R470.2, R480.2
unnamed: C188.2, IC65.9, R469.2
unnamed: C189.1, R469.1, R470.1, R471.2
unnamed: C190.1, IC66.1, R473.1, R477.1
unnamed: C190.2, IC66.2, R472.1
unnamed: C191.+, R472.2, R473.2, R474.1
unnamed: C192.2, IC66.6, R475.1
unnamed: C193.+, C194.+, R475.2, R476.2, R477.2
unnamed: C195.1, IC66.14, R479.2, R483.2
unnamed: C195.2, IC66.13, R478.2
unnamed: C196.+, R478.1, R479.1, R480.1
unnamed: C197.2, IC66.9, R481.2
unnamed: C198.+, C199.+, R481.1, R482.1, R483.1
unnamed: C200.2, IC67.2, R484.1
unnamed: C201.1, R484.2, R485.2, R486.1
unnamed: C202.1, IC67.7, R474.2, R488.1
unnamed: C202.2, IC67.6, R487.1
unnamed: C203.1, R487.2, R488.2, R489.1
unnamed: C200.1, IC67.1, R485.1, R492.2
unnamed: C204.1, IC67.14, R491.2, R495.2
unnamed: C204.2, IC67.13, R490.2
unnamed: C205.+, R490.1, R491.1, R492.1
unnamed: C206.2, IC67.9, R493.2
unnamed: C207.+, C208.+, R493.1, R494.1, R495.1
unnamed: C209.1, IC68.14, R497.2, R501.1
unnamed: C209.2, IC68.13, R496.2
unnamed: C210.1, R496.1, R497.1, R498.2
unnamed: C211.1, IC68.1, R500.1, R504.1
unnamed: C211.2, IC68.2, R499.1
unnamed: C212.+, R499.2, R500.2, R501.2
unnamed: C213.2, IC68.6, R502.1
unnamed: C214.+, C215.+, R502.2, R503.2, R504.2
unnamed: C216.1, IC68.8, R506.2, R516.2
unnamed: C216.2, IC68.9, R505.2
unnamed: C217.1, R505.1, R506.1, R507.2
unnamed: C218.1, IC69.1, R509.1, R513.1
unnamed: C218.2, IC69.2, R508.1
unnamed: C219.+, R508.2, R509.2, R510.1
unnamed: C220.2, IC69.6, R511.1
unnamed: C221.+, C222.+, R511.2, R512.2, R513.2
unnamed: C223.1, IC69.14, R515.2, R519.2
unnamed: C223.2, IC69.13, R514.2
unnamed: C224.+, R514.1, R515.1, R516.1
unnamed: C225.2, IC69.9, R517.2
unnamed: C226.+, C227.+, R517.1, R518.1, R519.1
unnamed: C228.2, IC70.2, R520.1
unnamed: C229.1, R520.2, R521.2, R522.1
unnamed: C230.1, IC70.7, R510.2, R524.1
unnamed: C230.2, IC70.6, R523.1
unnamed: C231.1, R523.2, R524.2, R525.1
unnamed: C228.1, IC70.1, R521.1, R528.2
unnamed: C232.1, IC70.14, R527.2, R531.2
unnamed: C232.2, IC70.13, R526.2
unnamed: C233.+, R526.1, R527.1, R528.1
unnamed: C234.2, IC70.9, R529.2
unnamed: C235.+, C236.+, R529.1, R530.1, R531.1
unnamed: C237.1, IC71.14, R533.2, R537.1
unnamed: C237.2, IC71.13, R532.2
unnamed: C238.1, R532.1, R533.1, R534.2
unnamed: C239.1, IC71.1, R536.1, R540.1
unnamed: C239.2, IC71.2, R535.1
unnamed: C240.+, R535.2, R536.2, R537.2
unnamed: C241.2, IC71.6, R538.1
unnamed: C242.+, C243.+, R538.2, R539.2, R540.2
unnamed: C244.1, IC71.8, R542.2, R552.2
unnamed: C244.2, IC71.9, R541.2
unnamed: C245.1, R541.1, R542.1, R543.2
unnamed: C246.1, IC72.1, R545.1, R549.1
unnamed: C246.2, IC72.2, R544.1
unnamed: C247.+, R544.2, R545.2, R546.1
unnamed: C248.2, IC72.6, R547.1
unnamed: C249.+, C250.+, R547.2, R548.2, R549.2
unnamed: C251.1, IC72.14, R551.2, R555.2
unnamed: C251.2, IC72.13, R550.2
unnamed: C252.+, R550.1, R551.1, R552.1
unnamed: C253.2, IC72.9, R553.2
unnamed: C254.+, C255.+, R553.1, R554.1, R555.1
unnamed: C256.2, IC73.2, R556.1
unnamed: C257.1, R556.2, R557.2, R558.1
unnamed: C258.1, IC73.7, R546.2, R560.1
unnamed: C258.2, IC73.6, R559.1
unnamed: C259.1, R559.2, R560.2, R561.1
unnamed: C256.1, IC73.1, R557.1, R564.2
unnamed: C260.1, IC73.14, R563.2, R567.2
unnamed: C260.2, IC73.13, R562.2
unnamed: C261.+, R562.1, R563.1, R564.1
unnamed: C262.2, IC73.9, R565.2
unnamed: C263.+, C264.+, R565.1, R566.1, R567.1
unnamed: C265.1, IC74.14, R569.2, R573.1
unnamed: C265.2, IC74.13, R568.2
unnamed: C266.1, R568.1, R569.1, R570.2
unnamed: C267.1, IC74.1, R572.1, R576.1
unnamed: C267.2, IC74.2, R571.1
unnamed: C268.+, R571.2, R572.2, R573.2
unnamed: C269.2, IC74.6, R574.1
unnamed: C270.+, C271.+, R574.2, R575.2, R576.2
unnamed: C272.1, IC74.8, R578.2, R588.2
unnamed: C272.2, IC74.9, R577.2
unnamed: C273.1, R577.1, R578.1, R579.2
unnamed: C274.1, IC75.1, R581.1, R585.1
unnamed: C274.2, IC75.2, R580.1
unnamed: C275.+, R580.2, R581.2, R582.1
unnamed: C276.2, IC75.6, R583.1
unnamed: C277.+, C278.+, R583.2, R584.2, R585.2
unnamed: C279.1, IC75.14, R587.2, R591.2
unnamed: C279.2, IC75.13, R586.2
unnamed: C280.+, R586.1, R587.1, R588.1
unnamed: C281.2, IC75.9, R589.2
unnamed: C282.+, C283.+, R589.1, R590.1, R591.1
unnamed: C284.2, IC76.2, R592.1
unnamed: C285.1, R592.2, R593.2, R594.1
unnamed: C286.1, IC76.7, R582.2, R596.1
unnamed: C286.2, IC76.6, R595.1
unnamed: C287.1, R595.2, R596.2, R597.1
unnamed: C284.1, IC76.1, R593.1, R600.2
unnamed: C288.1, IC76.14, R599.2, R603.2
unnamed: C288.2, IC76.13, R598.2
unnamed: C289.+, R598.1, R599.1, R600.1
unnamed: C290.2, IC76.9, R601.2
unnamed: C291.+, C292.+, R601.1, R602.1, R603.1
unnamed: C294.1, IC86.10, Y2.1
unnamed: C293.1, IC86.9, Y2.2
unnamed: C297.1, IC88.10, Y3.1
unnamed: C296.1, IC88.9, Y3.2
unnamed: C300.1, IC90.10, Y4.1
unnamed: C299.1, IC90.9, Y4.2
unnamed: C303.1, IC92.10, Y5.1
unnamed: C302.1, IC92.9, Y5.2
unnamed: C306.1, IC94.10, Y6.1
unnamed: C305.1, IC94.9, Y6.2
unnamed: C309.1, IC96.10, Y7.1
unnamed: C308.1, IC96.9, Y7.2
unnamed: C312.1, IC98.10, Y8.1
unnamed: C311.1, IC98.9, Y8.2
unnamed: C315.1, IC100.10, Y9.1
unnamed: C314.1, IC100.9, Y9.2
unnamed: C318.1, IC102.10, Y10.1
unnamed: C317.1, IC102.9, Y10.2
unnamed: C321.1, IC104.10, Y11.1
unnamed: C320.1, IC104.9, Y11.2
unnamed: C324.1, IC106.10, Y12.1
unnamed: C323.1, IC106.9, Y12.2
unnamed: C327.1, IC108.10, Y13.1
unnamed: C326.1, IC108.9, Y13.2
unnamed: C330.1, IC110.10, Y14.1
unnamed: C329.1, IC110.9, Y14.2
unnamed: C333.1, IC112.10, Y15.1
unnamed: C332.1, IC112.9, Y15.2
unnamed: C336.1, IC114.10, Y16.1
unnamed: C335.1, IC114.9, Y16.2
unnamed: C339.1, IC116.10, Y17.1
unnamed: C338.1, IC116.9, Y17.2
unnamed: C342.1, IC118.10, Y18.1
unnamed: C341.1, IC118.9, Y18.2
unnamed: C345.1, IC120.10, Y19.1
unnamed: C344.1, IC120.9, Y19.2
unnamed: C348.1, IC122.10, Y20.1
unnamed: C347.1, IC122.9, Y20.2
unnamed: C351.1, IC124.10, Y21.1
unnamed: C350.1, IC124.9, Y21.2
unnamed: C354.1, IC126.10, Y22.1
unnamed: C353.1, IC126.9, Y22.2
unnamed: C357.1, IC128.10, Y23.1
unnamed: C356.1, IC128.9, Y23.2
unnamed: C360.1, IC130.10, Y24.1
unnamed: C359.1, IC130.9, Y24.2
unnamed: C363.1, IC132.10, Y25.1
unnamed: C362.1, IC132.9, Y25.2
PWM01: IC86.15, IC134.1
PWM02: IC88.15, IC134.2
PWM03: IC90.15, IC134.3
PWM04: IC92.15, IC134.4
PWM05: IC94.15, IC134.5
PWM06: IC96.15, IC134.6
PWM07: IC98.15, IC134.7
PWM08: IC100.15, IC134.8
PWM09: IC102.15, IC135.1
PWM10: IC104.15, IC135.2
PWM11: IC106.15, IC135.3
PWM12: IC108.15, IC135.4
PWM13: IC110.15, IC135.5
PWM14: IC112.15, IC135.6
PWM15: IC114.15, IC135.7
PWM16: IC116.15, IC135.8
PWM17: IC118.15, IC136.1
PWM18: IC120.15, IC136.2
PWM19: IC122.15, IC136.3
PWM20: IC124.15, IC136.4
PWM21: IC126.15, IC136.5
PWM22: IC128.15, IC136.6
PWM23: IC130.15, IC136.7
PWM24: IC132.15, IC136.8
RESET00: IC1.1, ISP1.5, R1.2
RESET01: IC86.1, ISP2.5, R604.2
RESET02: IC88.1, ISP3.5, R605.2
RESET03: IC90.1, ISP4.5, R606.2
RESET04: IC92.1, ISP5.5, R607.2
RESET05: IC94.1, ISP6.5, R608.2
RESET06: IC96.1, ISP7.5, R609.2
RESET07: IC98.1, ISP8.5, R610.2
RESET08: IC100.1, ISP9.5, R611.2
RESET09: IC102.1, ISP10.5, R612.2
RESET10: IC104.1, ISP11.5, R613.2
RESET11: IC106.1, ISP12.5, R614.2
RESET12: IC108.1, ISP13.5, R615.2
RESET13: IC110.1, ISP14.5, R616.2
RESET14: IC112.1, ISP15.5, R617.2
RESET15: IC114.1, ISP16.5, R618.2
RESET16: IC116.1, ISP17.5, R619.2
RESET17: IC118.1, ISP18.5, R620.2
RESET18: IC120.1, ISP19.5, R621.2
RESET19: IC122.1, ISP20.5, R622.2
RESET20: IC124.1, ISP21.5, R623.2
RESET21: IC126.1, ISP22.5, R624.2
RESET22: IC128.1, ISP23.5, R625.2
RESET23: IC130.1, ISP24.5, R626.2
RESET24: IC132.1, ISP25.5, R627.2
RX00: IC1.2, J6.3
RX01: IC86.2, J7.3
RX02: IC88.2, J8.3
RX03: IC90.2, J9.3
RX04: IC92.2, J10.3
RX05: IC94.2, J11.3
RX06: IC96.2, J12.3
RX07: IC98.2, J13.3
RX08: IC100.2, J14.3
RX09: IC102.2, J15.3
RX10: IC104.2, J16.3
RX11: IC106.2, J17.3
RX12: IC108.2, J18.3
RX13: IC110.2, J19.3
RX14: IC112.2, J20.3
RX15: IC114.2, J21.3
RX16: IC116.2, J22.3
RX17: IC118.2, J23.3
RX18: IC120.2, J24.3
RX19: IC122.2, J25.3
RX20: IC124.2, J26.3
RX21: IC126.2, J27.3
RX22: IC128.2, J28.3
RX23: IC130.2, J29.3
RX24: IC132.2, J30.3
SCK00: IC1.19, IC2.3, IC86.19, IC88.19, IC90.19, IC92.19, IC94.19, IC96.19, IC98.19, IC100.19, IC102.19, IC104.19, IC106.19, IC108.19, IC110.19, IC112.19, IC114.19, IC116.19, IC118.19, IC120.19, IC122.19, IC124.19, IC126.19, IC128.19, IC130.19, IC132.19, ISP1.3, ISP2.3, ISP3.3, ISP4.3, ISP5.3, ISP6.3, ISP7.3, ISP8.3, ISP9.3, ISP10.3, ISP11.3, ISP12.3, ISP13.3, ISP14.3, ISP15.3, ISP16.3, ISP17.3, ISP18.3, ISP19.3, ISP20.3, ISP21.3, ISP22.3, ISP23.3, ISP24.3, ISP25.3
SEN00: J3.3, R246.1
SEN01: J3.4, R255.1
SEN02: J3.5, R273.2
SEN03: J3.6, R270.2
SEN04: J3.7, R282.1
SEN05: J3.8, R291.1
SEN06: J3.9, R309.2
SEN07: J3.10, R306.2
SEN08: J3.11, R318.1
SEN09: J3.12, R327.1
SEN10: J3.13, R345.2
SEN11: J3.14, R342.2
SEN12: J3.15, R354.1
SEN13: J3.16, R363.1
SEN14: J3.17, R381.2
SEN15: J3.18, R378.2
SEN16: J3.19, R390.1
SEN17: J3.20, R399.1
SEN18: J3.21, R417.2
SEN19: J3.22, R414.2
SEN20: J3.23, R426.1
SEN21: J3.24, R435.1
SEN22: J3.25, R453.2
SEN23: J3.26, R450.2
SEN24: J4.3, R462.1
SEN25: J4.4, R471.1
SEN26: J4.5, R489.2
SEN27: J4.6, R486.2
SEN28: J4.7, R498.1
SEN29: J4.8, R507.1
SEN30: J4.9, R525.2
SEN31: J4.10, R522.2
SEN32: J4.11, R534.1
SEN33: J4.12, R543.1
SEN34: J4.13, R561.2
SEN35: J4.14, R558.2
SEN36: J4.15, R570.1
SEN37: J4.16, R579.1
SUPPLY1_24V: C4.+, C5.+, IC3.1, J1.2
SUPPLY2_24V: C7.+, C8.+, IC4.1, J2.2
TX00: IC1.3, J6.2
TX01: IC86.3, J7.2
TX02: IC88.3, J8.2
TX03: IC90.3, J9.2
TX04: IC92.3, J10.2
TX05: IC94.3, J11.2
TX06: IC96.3, J12.2
TX07: IC98.3, J13.2
TX08: IC100.3, J14.2
TX09: IC102.3, J15.2
TX10: IC104.3, J16.2
TX11: IC106.3, J17.2
TX12: IC108.3, J18.2
TX13: IC110.3, J19.2
TX14: IC112.3, J20.2
TX15: IC114.3, J21.2
TX16: IC116.3, J22.2
TX17: IC118.3, J23.2
TX18: IC120.3, J24.2
TX19: IC122.3, J25.2
TX20: IC124.3, J26.2
TX21: IC126.3, J27.2
TX22: IC128.3, J28.2
TX23: IC130.3, J29.2
TX24: IC132.3, J30.2
VALVE01: IC134.18, J5.3
VALVE02: IC134.17, J5.4
VALVE03: IC134.16, J5.5
VALVE04: IC134.15, J5.6
VALVE05: IC134.14, J5.7
VALVE06: IC134.13, J5.8
VALVE07: IC134.12, J5.9
VALVE08: IC134.11, J5.10
VALVE09: IC135.18, J5.11
VALVE10: IC135.17, J5.12
VALVE11: IC135.16, J5.13
VALVE12: IC135.15, J5.14
VALVE13: IC135.14, J5.15
VALVE14: IC135.13, J5.16
VALVE15: IC135.12, J5.17
VALVE16: IC135.11, J5.18
VALVE17: IC136.18, J5.19
VALVE18: IC136.17, J5.20
VALVE19: IC136.16, J5.21
VALVE20: IC136.15, J5.22
VALVE21: IC136.14, J5.23
VALVE22: IC136.13, J5.24
VALVE23: IC136.12, J5.25
VALVE24: IC136.11, J5.26
